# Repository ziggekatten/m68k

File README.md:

# Note to myself: I hate C pointers and macros.......
I have an blog where I will post my progress and thoughts when I have some spare time: https://brorson.se
# m68k
A overambitious project to build a usable computer from scratch. Based on bits and pieces from the interwebb, but with my own twists and turns. This main README will change frequently when I change my mind and decisions. 

It's not the goal that matters, is the journey....and it's true. Getting your thoughts and ideas into circuits and code is an iterative process, and for each success you get satisfaction. For every failure.....you get a reason for a big drink and rethink your decisions, just to fix the issue and start an new iteration. Add oh boy, the satisfaction when your idea works...priceless! 

Some decisions made from my part:

- Assembler is fun in small doses, so my plan is to NOT write firmware in assembler, but instead go down the C route and messing with sections and linkerscripts. Reason beeing that this will make me learn not only the various segments and the ELF format, but also how the GCC/LLVM toolchains works in more detail. I would like to use Zig (primary) or Rust (secondary), but as an non compiler wizard, this is currently on the backfoot, and O'l trusted C will do. There are some challenges though, that are quite simple in assembler, but when using C and segregation of duty, requires some more thoughts. For example, when using interrupts on the serial line, how do you pass the input from the exceptionhandler to your main kernel code? Simple answer one would say, some defined pseudo registers monitored by your main code in combination of global variables/structs in C. But this comes at an cost of CPU cycles as stuff needs to pass memory in several stages. Not easy decisions. Also, as I'm building some built in monitoring stuff in the firmwware to see values of stack pointer and register values, I might need to add som asssembler in the end. It will be inline if that's the case. It hurts, but unless I can use some GCC low level stuff I probably need to do this.
- Build my own stdlib based on newlib (https://sourceware.org/newlib/)
- Serial interface and an HW-monitor as initial I/0 path to the SBC 

Initial hardware:
- CPU: MC68010@12MHz
- DUART: MC68681
- 2 * 512K FLASH ROM
- 2 x 512K SRAM
- A bunch of 74LS/HCT chips
- A bunch of breadboards
- Some PAL/GAL's to replace discrete glue logic in the end
- Reset circuitry based on 555 timer and with both a reset button as well as an single step function, using DTACK.

## Some loose thoughts
- Use ELF as a base segment standard instead of Motorola S-records. This means that i need to steal someone elses ELF loader I guess... 
- When basic serial I/O is done. It's time to look at keyboard input as well as graphics display. The keyboard stuff is easy enough if using PS/2 standard. The graphics stuff however is a little bit more complicated. Signal wise it is easy, just output the correct voltages and Bob's your uncle. But getting data in a format that does not bog down CPU to some memory mapped hardware, and the get the display circuit to effectively interpret data and do stuff, is a different story. Text based stuff are easy using predetermined fonts, but The 680x0 CPU is not capable to feed pixel data at rates needed if just pushing pixels, so there have to be stuff in between. Amigas, Ataris and others have this done in custom chips, which means that I have to do it in an similar way. But this is where I draw the line (pun intended) and don't design my own blitter, copper etc. I will probably interface to already done parts, using APIs or existing hardware designs. In the end, designing at this level means also supply low level libraries and stuff. However, an pure vector based drawing design is in my head, so one never know....

## Memory map of the design
I keep it simple, and plan using the VBR register in the MC68010, so there is no shadowing or moving of ROM in my design.

| Address                 | Description                                                             |
|-------------------------|-------------------------------------------------------------------------|
| 0x00000000 - 0x000FFFFF | ROM ( 2 x 512K)                                                         |
| 0x00100000 - 0x001FFFFF | Onboard RAM (1 MB)                                                      |
| 0x00200000 - 0x00CFFFFF | Space for additional (14 MB) RAM                                        |
| 0x00D00000 -            | I/O space  (2 MB)                                                       | 
| 0x00D00000 - 0x00D0FFFF | DUART (64KB)                                                            |

## Codebase
I have switched to use https://github.com/tomstorey/m68k_bare_metal as base for my project instead of inventing all by myself. Sure, my linkerscript, Makefile and stuff was not bad, but was very bare bone. Even if there are a little more assembly, the structure is is more usable as defining exception vectors and stuff are easier. So instead of continuing and reinvent the wheel, I made the choice to use som clever stuff from github. Tom, you made me see a different (and more professional) way of doing stuff by the way you structured your code. Especially the linkerscript was an huge improvement over my amateur cocktail of C code.

All old firmware code are now in the /old_stuff folder and all new under /mb68k_bare_metal/mb68k
My headerfiles used for my specific board is located under /mb68k_bare_metal/include

## Version history
0.1.10 - Use of new approach for using C and design wise introducing buffers and more GALs 

0.1.9 - A lot of reshuffeling

0.1.8 - Switched to PlatformIO for Arduino stuff

0.1.7 - Got the firmware to configure DUART and spit out stuff on the terminal in sim68000 using pure C. Hardware is tested in an sense that I can control the DUART from an Arduiono Mega, and the CPU stuff on the breadboard is free running, and are awaiting the pairing of DUART and firmware code.

0.1.6 - Cleaned upp some code and added some README stuff. All prototypes now in headers.

0.1.5 - Just cleaning stuff

0.1.4 - Milestone. Got my bare Firmware (just ending in an loop) running in sim68000

0.1.3 - Just a bunch of renaming and updates of README files. In essence, cleaning up my own mess

0.1.2 - Milestone. I finally got the grips on gcc, linkerscripts, .map files etc. Building an ELF and object dump an binary now generates binary file with an valid reset vector and correct sections copied to RAM. What a fun ride it have been.

0.1.1 - Milestone. Got a free running CPU stepping through memory and blinking leds, by tying databus to ground (all zeros) throug pulldown resistors

## Toolchain(s) and emulators/simulators
Currently using GCC on Ubuntu 20.04 cross compiled for m68k.
In parallel building an LLVM toolchain for exploring the capabilities of using Rust and/or Zig instead of C. This is somewhat in an experimental phase, as some basic compilation efforts on LLVM and Rust/Zig is currently beeing tried out. My toolchains run in docker, and Dockerfiles can be found in the [toolchains] folder.

## Folder structure
| Folder     | Description                                                                          |
|------------|--------------------------------------------------------------------------------------|
| code       | Code for firmware and other stuff goes in here                                       |
| kicad      | KiCAD 7.x schematics                                                                 |
| digital    | Digital simulator for messing with glue logic and generation WinCUPL code in the end |
| toolchains | Things related to toolchains. Docker files etc                                       |
| tests      | Arduino stuff used to test and program various parts of the design                   |

## Some experiences to share

MC68000/10 memory mapping and external pheripherals are always an challenge. That said, the m68k has the most beautiful register/memory layout and assembler syntax known to man. If todays CPU's had this layout, ohh man... Normally external peripherals only use a few address lines and more importantly only half the data bus (unless on an MC68008). What this means is that you really need to understand how the processor address memory and in which order it's doing stuff. First of all, as you might have noted on the CPU there is no address line of 0. First physical address line is A1, which will cause som confusion to newbies (as it did to me!). To explain this we need to understand two other physical pins on the CPU: UDS and LDS. UDS means Upper Data Strobe, and LDS means Lower Data Strobe. These pins define if you are in the upper 8-bit or lower 8-bit of an word (16 bit). 

Now, this is what caught me, since the CPU is Big Endeian, even adresses is always the upper 8-bits. Easiest way of explain this is by starting at at the lowest address in hex: 0x00000000. This is an even address, and accessing this address will assert the UDS-pin signaling that the upper 8-bits of the data bus will be read/written from/to (bit 15-8). When designing your memory map, things can be confusing. Let us say that memory 0x00000000 to 0x000FFFFF is your first MB of RAM, and you think that address 0x00100000 is the first byte in the I/O space, you would be wrong. Address 0x00100000 is the upper 8-bits of the 16-bit word, and if you have the pheriperal connected to the D0-D7, the effective address is actually 0x00100001!. 

What this means is, that you need to take care when accessing 8-bit memory mapped peripherals. Let us take an simple example here using the MC68681 DUART chip as an example. It has an 4-bit addressing bus for it's registers that we normally connect to A1-A4, and an 8-bit address bus, connected to the A0-A7 physical bus. According to the documentation the registers are one byte in between on the chip itself. 

But this is not true in the scope of the CPU, as the most significant byte is never seen by the chip. It sees A1, not A0(UDS). In effect, this means that your code needs to have an offset of two(2) whereas the chip has an offset of only one(1).
In general, working with bytes is an pain as you need to think about alignment, and if possible use words....

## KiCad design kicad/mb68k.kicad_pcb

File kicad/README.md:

# Hardware design

Basic principles:
- Use of buffers when in doubt. The 68010 pins can't drive that much current 

TODO: description

- CPU: MC68010@12MHz
- DUART: MC68681
- 2 * 512K FLASH ROM
- 2 x 512K SRAM

## Memory map

TODO: description

| Start address (hex) | End address (hex) | Usage                              |
|:-------------------:|:-----------------:|:----------------------------------:|
|0x00100000           |0x00200000         | Onboard RAM                        |
|0x00000000           |0x00100000         | Onboard ROM                        |

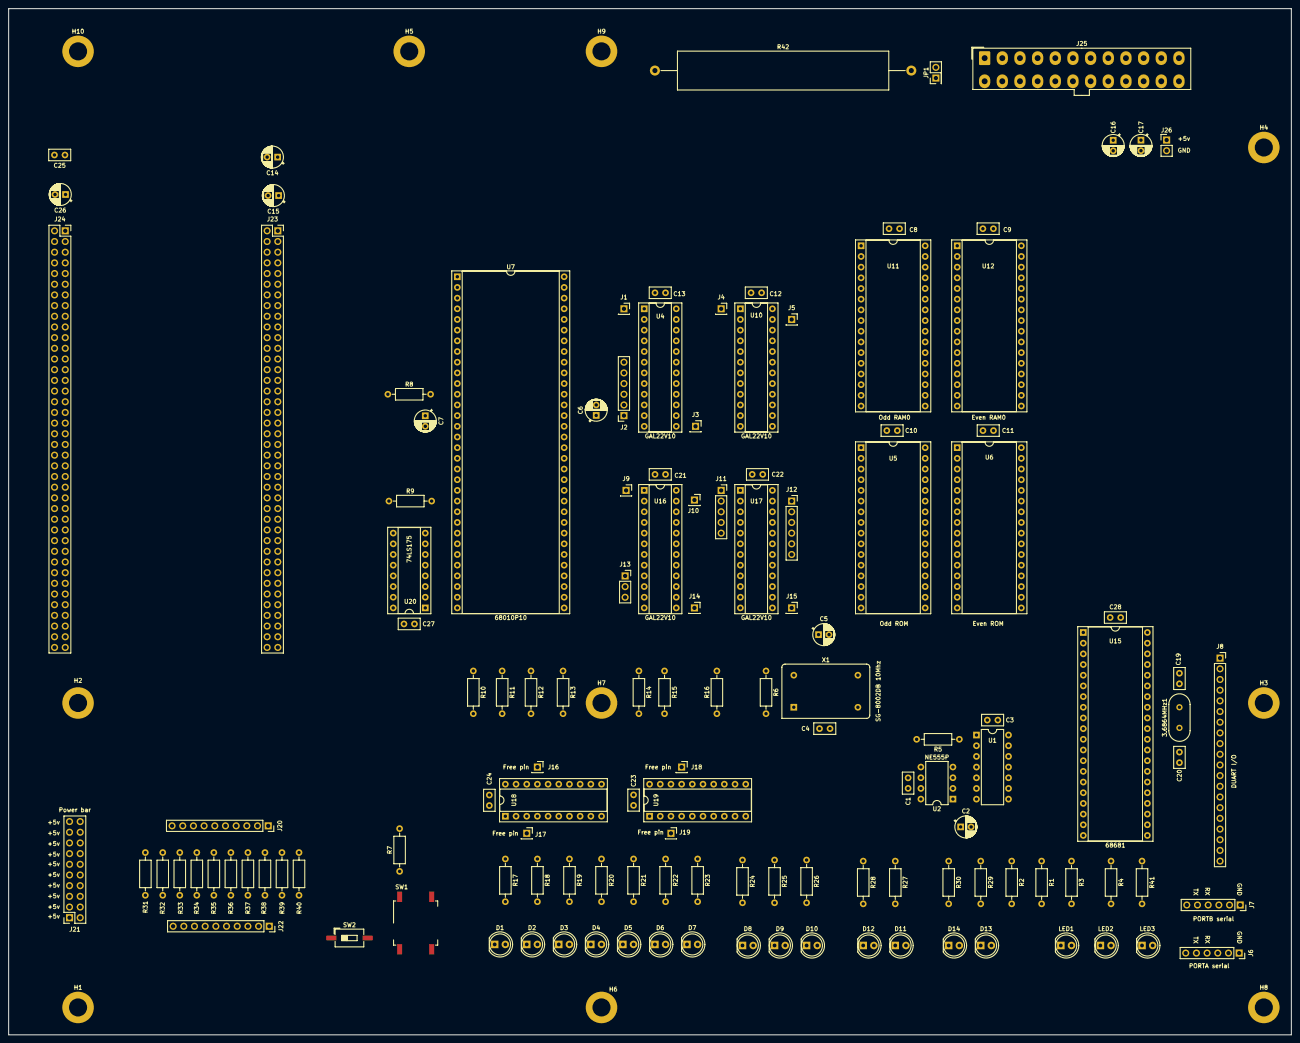
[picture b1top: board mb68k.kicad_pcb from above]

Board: 4 copper layers, 305.0 x 244.0 mm, 142 parts (0 on the bottom side), 199 nets, no tracks yet.

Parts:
3.6864MHz1: Crystal; Crystal_HC18-U_Vertical
C1, C3, C4, C8, C9, C10, C11, C12, C13, C21, C22, C23, C24, C27, C28: 100nF; C_Disc_D5.0mm_W2.5mm_P2.50mm
C2, C16: 100uF; CP_Radial_D5.0mm_P2.50mm
C5, C6, C7, C15, C26: 100nF; CP_Radial_D5.0mm_P2.50mm
C14: 10uF; CP_Radial_D5.0mm_P2.50mm
C17: 470uF; CP_Radial_D5.0mm_P2.50mm
C19, C20: 7pF; C_Disc_D5.0mm_W2.5mm_P2.50mm
C25: 10uF; C_Disc_D5.0mm_W2.5mm_P2.50mm
D1: IRQ1; LED_D5.0mm
D2: IRQ2; LED_D5.0mm
D3: IRQ3; LED_D5.0mm
D4: IRQ4; LED_D5.0mm
D5: IRQ5; LED_D5.0mm
D6: IRQ6; LED_D5.0mm
D7: IRQ7; LED_D5.0mm
D8: FC1; LED_D5.0mm
D9: FC2; LED_D5.0mm
D10: FC3; LED_D5.0mm
D11: DUARTA_RX; LED_D5.0mm
D12: DUARTA_TX; LED_D5.0mm
D13: DUARTB_RX; LED_D5.0mm
D14: DUARTB_TX; LED_D5.0mm
H1, H2, H3, H4, H5, H6, H7, H8, H9, H10: MountingHole_Pad; MountingHole_4.3mm_M4_DIN965_Pad
J1, J3, J4, J5, J9, J10, J14, J15, J16, J17, J18, J19: Free pin; PinSocket_1x01_P2.54mm_Vertical
J2, J12: Free pins; PinSocket_1x06_P2.54mm_Vertical
J6: PORTA serial; PinSocket_1x06_P2.54mm_Vertical
J7: PORTB serial; PinSocket_1x06_P2.54mm_Vertical
J8: DUART I/O; PinSocket_1x20_P2.54mm_Vertical
J11: Free Pins; PinSocket_1x05_P2.54mm_Vertical
J13: Free pins; PinSocket_1x03_P2.54mm_Vertical
J20, J22: Spare resistors; PinSocket_1x10_P2.54mm_Vertical
J21: Power bar; PinSocket_2x10_P2.54mm_Vertical
J23: BUS Slot 2; PinSocket_2x40_P2.54mm_Vertical
J24: BUS Slot 1; PinSocket_2x40_P2.54mm_Vertical
J25: ATX-24; Molex_Mini-Fit_Jr_5566-24A_2x12_P4.20mm_Vertical
J26: External Power; PinHeader_1x02_P2.54mm_Vertical
JP1: BASE LOAD; PinHeader_2x01_P2.54mm_Vertical
LED1: RED Reset; LED_D5.0mm
LED2: GREEN Run; LED_D5.0mm
LED3: GREEN PWR; LED_D5.0mm
R1, R2, R6: 4K7; R_Axial_DIN0207_L6.3mm_D2.5mm_P10.16mm_Horizontal
R3, R4: 330R; R_Axial_DIN0207_L6.3mm_D2.5mm_P10.16mm_Horizontal
R5: 2K2; R_Axial_DIN0207_L6.3mm_D2.5mm_P10.16mm_Horizontal
R7: 270R; R_Axial_DIN0207_L6.3mm_D2.5mm_P10.16mm_Horizontal
R8, R9, R10, R11, R12, R13, R14, R15, R16, R31, R32, R33, R34, R35, R36, R37, R38, R39, R40: 4k7; R_Axial_DIN0207_L6.3mm_D2.5mm_P10.16mm_Horizontal
R17, R18, R19, R20, R21, R22, R23, R24, R25, R26, R27, R28, R29, R30, R41: R330; R_Axial_DIN0207_L6.3mm_D2.5mm_P10.16mm_Horizontal
R42: R10 14W; R_Axial_Power_L50.0mm_W9.0mm_P60.96mm
SW1: HW_RESET_SW; SW_MEC_5GSH9
SW2: POWER ON; SW_DIP_SPSTx01_Slide_6.7x4.1mm_W8.61mm_P2.54mm_LowProfile
U1: 74LS05; DIP-14_W7.62mm
U2: NE555P; DIP-8_W7.62mm
U4, U10, U16, U17: GAL22V10; DIP-24_W7.62mm_Socket
U5, U6: SST39SF040; DIP-32_W15.24mm_Socket
U7: 68010P10; DIP-64_W25.4mm_Socket
U11, U12: AS6C4008-55PCN; DIP-32_W15.24mm_Socket
U15: 68681; DIP-40_W15.24mm_Socket
U18, U19: 74LS244; DIP-20_W7.62mm_Socket
U20: 74LS175; DIP-16_W7.62mm_Socket
X1: SG-8002DB 10Mhz; Oscillator_DIP-14

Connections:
A1: J23.47, J24.47, U5.12 (A0), U6.12 (A0), U7.29 (A1), U11.12 (A0), U12.12 (A0), U15.1 (RS1), U16.5 (I4)
A2: J23.45, J24.45, U5.11 (A1), U6.11 (A1), U7.30 (A2), U11.11 (A1), U12.11 (A1), U15.3 (RS2), U16.6 (I5)
A3: J23.43, J24.43, U5.10 (A2), U6.10 (A2), U7.31 (A3), U11.10 (A2), U12.10 (A2), U15.5 (RS3), U16.7 (I6)
A4: J23.41, J24.41, U5.9 (A3), U6.9 (A3), U7.32 (A4), U11.9 (A3), U12.9 (A3), U15.6 (RS4)
A5: J23.39, J24.39, U5.8 (A4), U6.8 (A4), U7.33 (A5), U11.8 (A4), U12.8 (A4)
A6: J23.37, J24.37, U5.7 (A5), U6.7 (A5), U7.34 (A6), U11.7 (A5), U12.7 (A5)
A7: J23.35, J24.35, U5.6 (A6), U6.6 (A6), U7.35 (A7), U11.6 (A6), U12.6 (A6)
A8: J23.33, J24.33, U5.5 (A7), U6.5 (A7), U7.36 (A8), U11.5 (A7), U12.5 (A7)
A9: J23.31, J24.31, U5.27 (A8), U6.27 (A8), U7.37 (A9), U11.27 (A8), U12.27 (A8)
A10: J23.29, J24.29, U5.26 (A9), U6.26 (A9), U7.38 (A10), U11.26 (A9), U12.26 (A9)
A11: J23.27, J24.27, U5.23 (A10), U6.23 (A10), U7.39 (A11), U11.23 (A10), U12.23 (A10)
A12: J23.25, J24.25, U5.25 (A11), U6.25 (A11), U7.40 (A12), U11.25 (A11), U12.25 (A11)
A13: J23.23, J24.23, U5.4 (A12), U6.4 (A12), U7.41 (A13), U11.4 (A12), U12.4 (A12)
A14: J23.21, J24.21, U5.28 (A13), U6.28 (A13), U7.42 (A14), U11.28 (A13), U12.28 (A13)
A15: J23.19, J24.19, U5.29 (A14), U6.29 (A14), U7.43 (A15), U11.3 (A14), U12.3 (A14)
A16: J23.17, J24.17, U5.3 (A15), U6.3 (A15), U7.44 (A16), U10.10 (I9), U11.31 (A15), U12.31 (A15)
A17: J23.15, J24.15, U5.2 (A16), U6.2 (A16), U7.45 (A17), U10.11 (I10), U11.2 (A16), U12.2 (A16)
A18: J23.13, J24.13, U5.30 (A17), U6.30 (A17), U7.46 (A18), U10.14 (I/O), U11.30 (A17), U12.30 (A17)
A19: J23.11, J24.11, U5.1 (A18), U6.1 (A18), U7.47 (A19), U10.15 (I/O), U11.1 (A18), U12.1 (A18)
A20: J23.9, J24.9, U7.48 (A20), U10.2 (I1)
A21: J23.7, J24.7, U7.50 (A21), U10.3 (I2)
A22: J23.5, J24.5, U7.51 (A22), U10.4 (I3)
A23: J23.3, J24.3, U7.52 (A23), U10.5 (I4)
CLK: J23.4, J24.4, U7.15 (CLK), X1.8 (OUT)
D0: J23.40, J24.40, U5.13 (D0), U7.5 (D0), U11.13 (DQ0), U15.25 (D0)
D1: J23.38, J24.38, U5.14 (D1), U7.4 (D1), U11.14 (DQ1), U15.16 (D1)
D2: J23.36, J24.36, U5.15 (D2), U7.3 (D2), U11.15 (DQ2), U15.24 (D2)
D3: J23.34, J24.34, U5.17 (D3), U7.2 (D3), U11.17 (DQ3), U15.17 (D3)
D4: J23.32, J24.32, U5.18 (D4), U7.1 (D4), U11.18 (DQ4), U15.23 (D4)
D5: J23.58, J24.58, U5.19 (D5), U7.64 (D5), U11.19 (DQ5), U15.18 (D5)
D6: J23.60, J24.60, U5.20 (D6), U7.63 (D6), U11.20 (DQ6), U15.22 (D6)
D7: J23.62, J24.62, U5.21 (D7), U7.62 (D7), U11.21 (DQ7), U15.19 (D7)
D8: J23.64, J24.64, U6.13 (D0), U7.61 (D8), U12.13 (DQ0)
D9: J23.66, J24.66, U6.14 (D1), U7.60 (D9), U12.14 (DQ1)
D10: J23.68, J24.68, U6.15 (D2), U7.59 (D10), U12.15 (DQ2)
D11: J23.70, J24.70, U6.17 (D3), U7.58 (D11), U12.17 (DQ3)
D12: J23.72, J24.72, U6.18 (D4), U7.57 (D12), U12.18 (DQ4)
D13: J23.74, J24.74, U6.19 (D5), U7.56 (D13), U12.19 (DQ5)
D14: J23.76, J24.76, U6.20 (D6), U7.55 (D14), U12.20 (DQ6)
D15: J23.78, J24.78, U6.21 (D7), U7.54 (D15), U12.21 (DQ7)
E: U7.20 (E), U20.9 (Cp)
FC0: U7.28 (FC0), U16.2 (I1), U19.2 (I0a)
FC1: U7.27 (FC1), U16.3 (I2), U19.4 (I1a)
FC2: U7.26 (FC2), U16.4 (I3), U19.6 (I2a)
GND: C2.2, C3.2, C4.2, C5.2, C6.2, C7.2, C8.2, C9.2, C10.2, C11.2, C12.2, C13.2, C14.2, C15.2, C16.2, C17.2, C19.1, C20.1, C21.2, C22.2, C23.2, C24.2, C25.2, C26.2, C27.1, C28.2, H1.1, H2.1, H3.1, H4.1, H5.1, H6.1, H7.1, H8.1, H9.1, H10.1, J6.1, J7.1, J8.1, J21.2, J21.4, J21.6, J21.8, J21.10, J21.12, J21.14, J21.16, J21.18, J21.20, J23.2, J23.42, J24.2, J24.42, J25.3 (GND), J25.5 (GND), J25.7 (GND), J25.15 (GND), J25.17 (GND), J25.18 (GND), J25.19 (GND), J25.24 (GND), JP1.1 (A), R7.2, R24.1, R25.1, R26.1, R27.1, R28.1, R29.1, R30.1, R41.1, SW2.1 (A), U1.7 (GND), U2.1 (GND), U4.12 (GND), U5.16 (GND), U6.16 (GND), U7.16 (GND), U7.53 (GND), U10.12 (GND), U11.16 (VSS), U12.16 (VSS), U15.20 (GND), U16.12 (GND), U17.12 (GND), U18.1 (OEa), U18.10 (GND), U18.19 (OEb), U19.1 (OEa), U19.10 (GND), U19.19 (OEb), U20.8 (GND), X1.7 (GND)
IP0: J8.2, U15.7 (IP0)
IP1: J8.3, U15.4 (IP1)
IP2: J8.4, U15.36 (IP2)
IP3: J8.5, U15.2 (IP3)
IP4: J8.6, U15.39 (IP4)
IP5: J8.7, U15.38 (IP5)
unnamed: D1.2 (A), R17.2
unnamed: D1.1 (K), U18.18 (O0a)
unnamed: D2.2 (A), R18.2
unnamed: D2.1 (K), U18.16 (O1a)
unnamed: D3.2 (A), R19.2
unnamed: D3.1 (K), U18.14 (O2a)
unnamed: D4.2 (A), R20.2
unnamed: D4.1 (K), U18.12 (O3a)
unnamed: D5.2 (A), R21.2
unnamed: D5.1 (K), U18.9 (O0b)
unnamed: D6.2 (A), R22.2
unnamed: D6.1 (K), U18.7 (O1b)
unnamed: D7.2 (A), R23.2
unnamed: D7.1 (K), U18.5 (O2b)
unnamed: D8.2 (A), U19.18 (O0a)
unnamed: D8.1 (K), R24.2
unnamed: D9.2 (A), U19.16 (O1a)
unnamed: D9.1 (K), R25.2
unnamed: D10.2 (A), U19.14 (O2a)
unnamed: D10.1 (K), R26.2
unnamed: D11.2 (A), U19.12 (O3a)
unnamed: D11.1 (K), R27.2
unnamed: D12.2 (A), U19.9 (O0b)
unnamed: D12.1 (K), R28.2
unnamed: D13.2 (A), U19.7 (O1b)
unnamed: D13.1 (K), R29.2
unnamed: D14.2 (A), U19.5 (O2b)
unnamed: D14.1 (K), R30.2
unnamed: J1.1, U4.1 (I0/CLK)
unnamed: J2.1, U4.11 (I10)
unnamed: J2.2, U4.10 (I9)
unnamed: J2.3, U4.9 (I8)
unnamed: J2.4, U4.8 (I7)
unnamed: J2.5, U4.7 (I6)
unnamed: J2.6, U4.6 (I5)
unnamed: J3.1, U4.13 (I11)
unnamed: J4.1, U10.1 (I0/CLK)
unnamed: J5.1, U10.23 (I/O)
unnamed: J9.1, U16.1 (I0/CLK)
unnamed: J10.1, U16.23 (I/O)
unnamed: J11.1, U17.1 (I0/CLK)
unnamed: J11.2, U17.2 (I1)
unnamed: J11.3, U17.3 (I2)
unnamed: J11.4, U17.4 (I3)
unnamed: J11.5, U17.5 (I4)
unnamed: J12.1, U17.23 (I/O)
unnamed: J12.2, U17.22 (I/O)
unnamed: J12.3, U17.21 (I/O)
unnamed: J12.4, U17.20 (I/O)
unnamed: J12.5, U17.19 (I/O)
unnamed: J12.6, U17.18 (I/O)
unnamed: J13.1, U16.9 (I8)
unnamed: J13.2, U16.10 (I9)
unnamed: J13.3, U16.11 (I10)
unnamed: J14.1, U16.13 (I11)
unnamed: J15.1, U17.13 (I11)
unnamed: J16.1, U18.17 (I3b)
unnamed: J17.1, U18.3 (O3b)
unnamed: J18.1, U19.17 (I3b)
unnamed: J19.1, U19.3 (O3b)
unnamed: J20.1, R40.2
unnamed: J20.2, R39.2
unnamed: J20.3, R38.2
unnamed: J20.4, R37.2
unnamed: J20.5, R36.2
unnamed: J20.6, R35.2
unnamed: J20.7, R34.2
unnamed: J20.8, R33.2
unnamed: J20.9, R32.2
unnamed: J20.10, R31.2
unnamed: J22.1, R40.1
unnamed: J22.2, R39.1
unnamed: J22.3, R38.1
unnamed: J22.4, R37.1
unnamed: J22.5, R36.1
unnamed: J22.6, R35.1
unnamed: J22.7, R34.1
unnamed: J22.8, R33.1
unnamed: J22.9, R32.1
unnamed: J22.10, R31.1
unnamed: J25.16 (PS_ON#), SW2.2 (B)
unnamed: J25.8 (PWR_OK), LED3.2 (A)
unnamed: JP1.2 (B), R42.2
unnamed: LED1.2 (A), R3.2
unnamed: LED2.2 (A), R4.2
unnamed: LED2.1 (K), U1.6
unnamed: LED3.1 (K), R41.2
unnamed: R7.1, SW1.1
unnamed: C2.1, R5.2, SW1.3 (K), U2.2 (TR), U2.6 (THR)
unnamed: C1.2, U2.5 (CV)
unnamed: U1.1, U1.3, U2.3 (Q)
unnamed: R8.2, U7.12 (BGACK), U7.13 (BR), U7.21 (VPA)
unnamed: 3.6864MHz1.1, C20.2, U15.32 (X1/CLK)
unnamed: 3.6864MHz1.2, C19.2, U15.33 (X2)
unnamed: U20.2 (Q0), U20.5 (D1)
unnamed: U20.7 (Q1), U20.12 (D2)
unnamed: U20.10 (Q2), U20.13 (D3)
unnamed: R6.2, X1.1 (OE)
OP0: J8.12, U15.29 (OP0)
OP1: J8.13, U15.12 (OP1)
OP2: J8.14, U15.28 (OP2)
OP3: J8.15, U15.13 (OP3)
OP4: J8.16, U15.27 (OP4)
OP5: J8.17, U15.14 (OP5)
OP6: J8.18, U15.26 (OP6)
OP7: J8.19, U15.15 (OP7)
RXDA: J6.4, J8.10, U15.31 (RXDA), U19.8 (I3a)
RXDB: J7.4, J8.8, U15.10 (RXDB), U19.13 (I1b)
R/~W: U4.4 (I3), U7.9 (R/W), U10.8 (I7)
TXDA: J6.5, J8.11, U15.30 (TXDA), U19.11 (I0b)
TXDB: J7.5, J8.9, U15.11 (TXDB), U19.15 (I2b)
VCC: C1.1, C3.1, C4.1, C5.1, C6.1, C7.1, C8.1, C9.1, C10.1, C11.1, C12.1, C13.1, C14.1, C15.1, C16.1, C17.1, C21.1, C22.1, C23.1, C24.1, C25.1, C26.1, C27.2, C28.1, J8.20, J21.1, J21.3, J21.5, J21.7, J21.9, J21.11, J21.13, J21.15, J21.17, J21.19, J23.1, J23.49, J24.1, J24.49, J25.4 (+5V), J25.6 (+5V), J25.21 (+5V), J25.22 (+5V), J25.23 (+5V), J26.1, J26.2, R1.1, R2.1, R3.1, R4.1, R5.1, R6.1, R8.1, R9.1, R10.1, R11.1, R12.1, R13.1, R14.1, R15.1, R16.1, R17.1, R18.1, R19.1, R20.1, R21.1, R22.1, R23.1, R42.1, U1.14 (VCC), U2.4 (R), U2.8 (VCC), U4.24 (VCC), U5.31 (PGM), U5.32 (VCC), U6.31 (PGM), U6.32 (VCC), U7.14 (VCC), U7.49 (VCC), U10.24 (VCC), U11.32 (VCC), U12.32 (VCC), U15.40 (VCC), U16.24 (VCC), U17.24 (VCC), U18.20 (VCC), U19.20 (VCC), U20.16 (VCC), X1.14 (Vcc)
_AS: U4.19 (I/O), U20.1 (~Mr), U20.4 (D0)
_R/~W: J23.20, J24.20, U4.16 (I/O), U11.29 (WE#), U12.29 (WE#), U15.8 (R/W)
_W/~R: U4.18 (I/O), U5.24 (OE), U6.24 (OE), U11.24 (OE#), U12.24 (OE#)
~AS: U4.2 (I1), U7.6 (AS), U10.13 (I11), U16.8 (I7)
~BERR: R9.2, U7.22 (BERR), U20.14 (~Q3)
~CSEVENRAM0: U10.19 (I/O), U12.22 (CE#)
~CSEVENROM: U6.22 (CE), U10.17 (I/O)
~CSODDRAM0: U10.18 (I/O), U11.22 (CE#)
~CSODDROM: U5.22 (CE), U10.16 (I/O)
~DTACK: J23.12, J24.12, U7.10 (DTACK), U10.21 (I/O), U15.9 (DTACK)
~DUARTSEL: U10.20 (I/O), U15.35 (CS)
~EXTSEL: J23.18, J24.18, U10.22 (I/O)
~HALT: R2.2, U1.4, U1.5, U7.17 (HALT)
~IACK1: J23.63, J24.63, U16.15 (I/O)
~IACK2: J23.61, J24.61, U16.16 (I/O)
~IACK3: J23.59, J24.59, U16.17 (I/O)
~IACK4: J23.57, J24.57, U16.19 (I/O)
~IACK5: J23.55, J24.55, U15.37 (IACK), U16.20 (I/O)
~IACK6: J23.53, J24.53, U16.21 (I/O)
~IACK7: J23.51, J24.51, U16.18 (I/O), U16.22 (I/O)
~IPL0: U7.25 (IPL0), U17.15 (I/O)
~IPL1: U7.24 (IPL1), U17.16 (I/O)
~IPL2: U7.23 (IPL2), U17.17 (I/O)
~IRQ1: J23.56, J24.56, R10.2, U17.6 (I5), U18.2 (I0a)
~IRQ2: J23.54, J24.54, R11.2, U17.7 (I6), U18.4 (I1a)
~IRQ3: J23.52, J24.52, R12.2, U17.8 (I7), U18.6 (I2a)
~IRQ4: J23.50, J24.50, R13.2, U17.9 (I8), U18.8 (I3a)
~IRQ5: J23.48, J24.48, R14.2, U15.21 (IRQ), U17.10 (I9), U18.11 (I0b)
~IRQ6: J23.46, J24.46, R15.2, U17.11 (I10), U18.13 (I1b)
~IRQ7: J23.44, J24.44, R16.2, U17.14 (I/O), U18.15 (I2b)
~LDS: U4.3 (I2), U7.8 (LDS), U10.7 (I6)
~RESET: LED1.1 (K), R1.2, U1.2, U7.18 (RESET), U15.34 (RESET)
~UDS: U4.5 (I4), U7.7 (UDS), U10.9 (I8)
~_AS: J23.26, J24.26, U4.14 (I/O)
~_LDS: J23.22, J24.22, U4.15 (I/O)
~_UDS: J23.24, J24.24, U4.17 (I/O)

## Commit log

2022-02-06 initial messing with digital and kicad
2023-01-26 cleanup of a mess on my desktop
2023-01-26 Added Dockerfiles
2023-01-26 README update
2023-01-26 Fixed user in Dockerfile.rosco
2023-01-26 Fixed DOckerfile.rosco
2023-01-27 First add of C-code
2023-01-27 cleanup
2023-01-27 Added vectors
2023-01-27 Added some vectors
2023-01-27 More handlers
2023-01-27 Even more vectors...
2023-01-27 Last vectors
2023-01-28 Renaimng and structuring
2023-01-28 Linker file created
2023-01-28 added copying of data and bss sections to ram
2023-01-28 Updated rosco Dockerfile
2023-01-29 Structuring of header file location
2023-01-29 Structuring of include location
2023-01-29 CLeaned up comments and namig standard
2023-01-29 cleaned upp comments in hwdefs
2023-01-29 Adden .bin in makefile and cleaned comments in boot.c
2023-01-29 added .gitignore
2023-01-29 Modified makefile
2023-01-30 Started serial stuff
2023-01-30 Serial stuff
2023-01-30 added some readme
2023-01-30 Added simulators
2023-01-30 moved some stuff into folders
2023-01-30 README...
2023-01-30 README again!
2023-01-30 Some prototype changes
2023-01-31 Updated readme and boot.h
2023-01-31 change to _fmain() for default entry
2023-01-31 README again
2023-01-31 .gitiignore
2023-01-31 Minor updates of README
2023-01-31 Updated Makefile
2023-01-31 Added functions to put char onto the DUART
2023-02-01 Arduion code asjustments
2023-02-01 Adjuste arduino code
2023-02-01 more arduion stuff
2023-02-01 Adjusted arduino with high impedence
2023-02-01 arduini again...
2023-02-01 Added some serial IO stuff
2023-02-02 Some additional comments added to code
2023-02-03 Added arduino DUART testcode
2023-02-03 Update README in root Update of comments in .h and .c files
2023-02-04 Intellisense
2023-02-06 Arduino and kicad work
2023-02-07 revamped arduino stuff
2023-02-11 Lot of stuff. Memmory decoder in GAL Added README for Digital Updated sketch for Arduino
2023-02-11 Added GAl pins
2023-02-13 KiCad updates
2023-02-13 remove temp files
2023-02-15 switched to PlatformIO fromArduino IDE
2023-02-15 Removed old arduino stuff
2023-02-15 Arduino tweaks
2023-02-15 Arduion tweaks
2023-02-15 Update kicad
2023-02-16 started with pcb
2023-02-16 Update footprint
2023-02-20 I hate pointers....
2023-02-20 update some code
2023-02-20 code fixes
2023-02-20 commented code
2023-02-20 first successful serial output
2023-02-20 test code
2023-02-22 Updated some comments
2023-02-22 Minor updates with comments on what to do
2023-02-22 Release of 1.7
2023-02-22 stupid errrors
2023-02-23 new branch
2023-02-23 update comments
2023-02-26 some cleanups
2023-03-23 updated .gitignore
2023-03-28 Messing with getchar
2023-03-29 messing with pointers
2023-12-19 new approach
2023-12-25 Revamped gluelogic for IRQ and DTACK
2023-12-25 Fixing bugs
2023-12-28 - Added buffers for LED indicators in kicad - Removed pullups on FC0.2 in kicad - Connected FC0-2 to glue logic in kicad - Revamped glue logic for irg and iack in Digital
2023-12-29 New decoding and GALs
2024-01-01 Added Bus error handling
2024-01-01 Changed DUART base I/O
2024-01-02 switched to GALasm
2024-01-02 finalized signaling PLD
2024-01-02 added footprints
2024-01-05 restructuring
2024-01-05 messing with gitignore
2024-01-05 further tweaks
2024-01-05 arggghhh!!
2024-01-05 moved header files
2024-01-06 PCB to ATX size
2024-01-07 saving state
2024-01-07 saved again
2024-01-07 saving kicad
2024-01-09 fiddlign with placement
2024-01-14 got irq to work
2024-01-14 shuffeling of code
2024-01-15 started parsing command
2024-01-19 restructuring of functions
2024-01-20 using struct for serial data
2024-01-20 staretd with parsin of commands
2024-01-20 buffer oveflow stuff
2024-01-20 buffer overflow protection
2024-01-21 passing struc pointers
2024-01-21 some cleanup
2024-01-21 messing with memory reads
2024-01-22 using pointer arithmetic
2024-01-22 Cleaning up stuff
2024-01-23 cleanups
2024-01-29 revamp of parser
2024-01-29 lot of stupid stuff with structs
